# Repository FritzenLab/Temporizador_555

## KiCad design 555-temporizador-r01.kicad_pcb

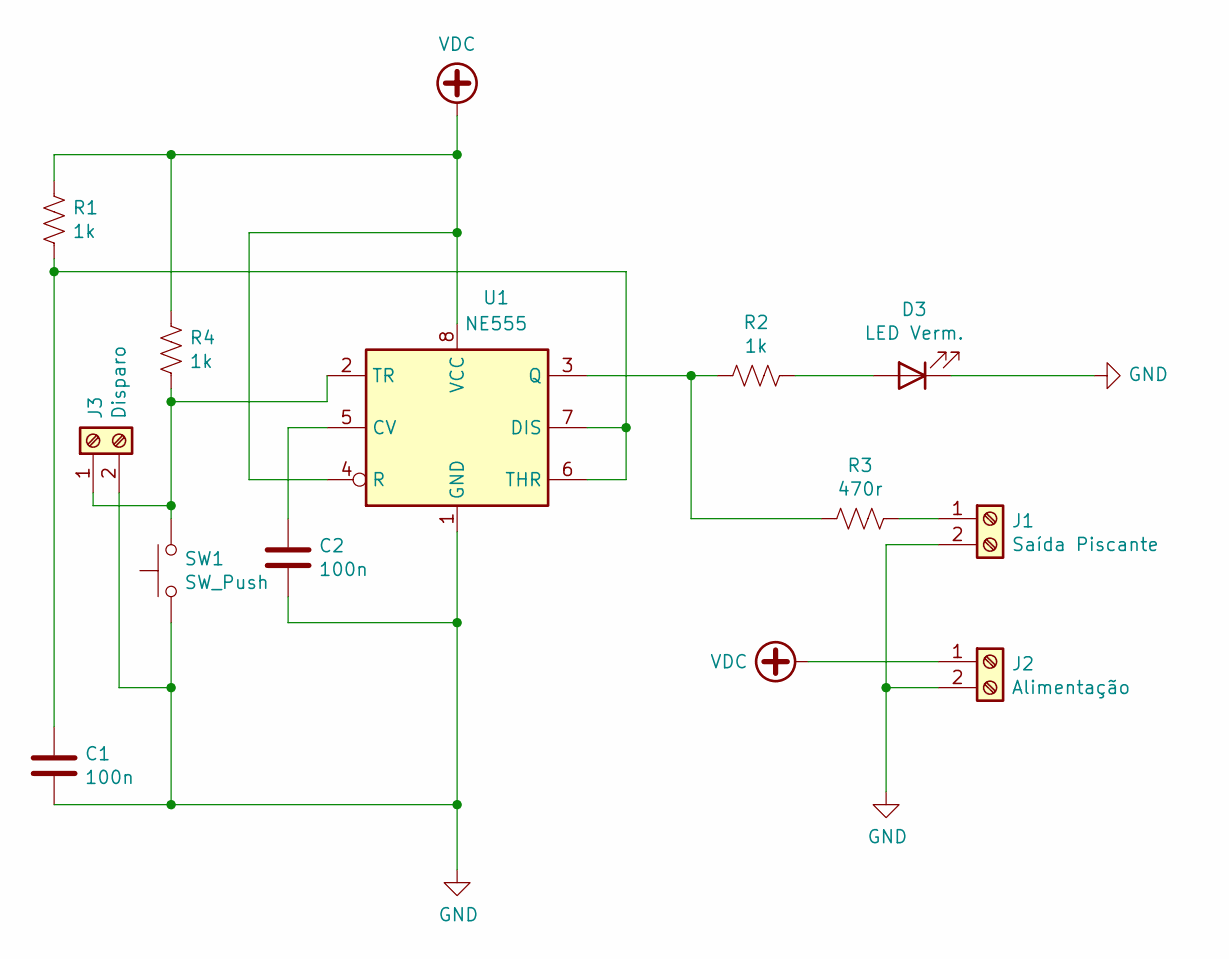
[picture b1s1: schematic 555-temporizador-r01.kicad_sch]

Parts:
C1, C2: 100n; C_Disc_D3.0mm_W2.0mm_P2.50mm
D3: LED Verm.; LED_D5.0mm_Clear
J1: Saída Piscante; PhoenixContact_MCV_1,5_2-G-5.08_1x02_P5.08mm_Vertical
J2: Alimentação; PhoenixContact_MCV_1,5_2-G-5.08_1x02_P5.08mm_Vertical
J3: Disparo; PhoenixContact_MCV_1,5_2-G-5.08_1x02_P5.08mm_Vertical
R1, R2, R4: 1k; R_Axial_DIN0207_L6.3mm_D2.5mm_P10.16mm_Horizontal
R3: 470r; R_Axial_DIN0207_L6.3mm_D2.5mm_P10.16mm_Horizontal
SW1: SW_Push; SW_PUSH_6mm
U1: NE555; DIP-8_W7.62mm_Socket_LongPads

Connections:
GND: C1.2, C2.2, D3.1 (K), J1.2, J2.2, J3.2, SW1.1, U1.1 (GND)
unnamed: D3.2 (A), R2.1
unnamed: J1.1, R3.1
unnamed: J3.1, R4.2, SW1.2, U1.2 (TR)
unnamed: C2.1, U1.5 (CV)
unnamed: C1.1, R1.2, U1.6 (THR), U1.7 (DIS)
unnamed: R2.2, R3.2, U1.3 (Q)
VDC: J2.1, R1.1, R4.1, U1.4 (R), U1.8 (VCC)

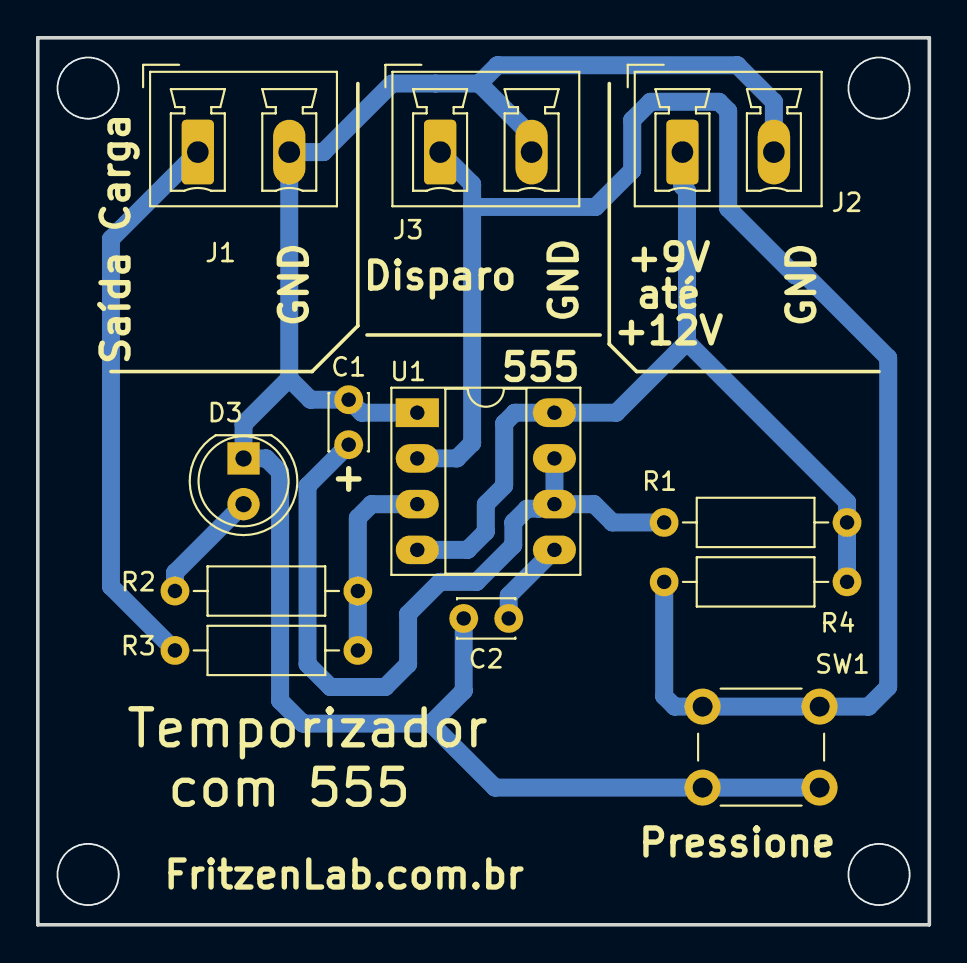
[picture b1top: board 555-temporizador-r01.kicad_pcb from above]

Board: 2 copper layers, 49.5 x 49.3 mm, 12 parts (0 on the bottom side), 8 nets.

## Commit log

2016-03-02 Lançamento inicial de arquivos
    Upload inicial de diagrama esquematico e placa (layout) do temporizador
    educacional baseado no CI 555, em formato Eagle CAD
2016-04-01 Primeira revisao (r00) e arquivos para fabricacao
    Primeira revisao (estética e troca do conector da fonte por um KRE 5mm).
    Gerados Gerber para fabricaçao da PCI
2016-05-05 Upload de arquivos atuais que já foram para produção
    Upload de arquivos atuais que já foram produzidos
2016-05-05 Upload de arquivos atuais que foram para produção
    Upload de arquivos atuais que foram para produção
2019-02-10 revisao da PCI
    revisao da PCI
2024-11-03 generated gerbers r02
2024-11-03 added images
